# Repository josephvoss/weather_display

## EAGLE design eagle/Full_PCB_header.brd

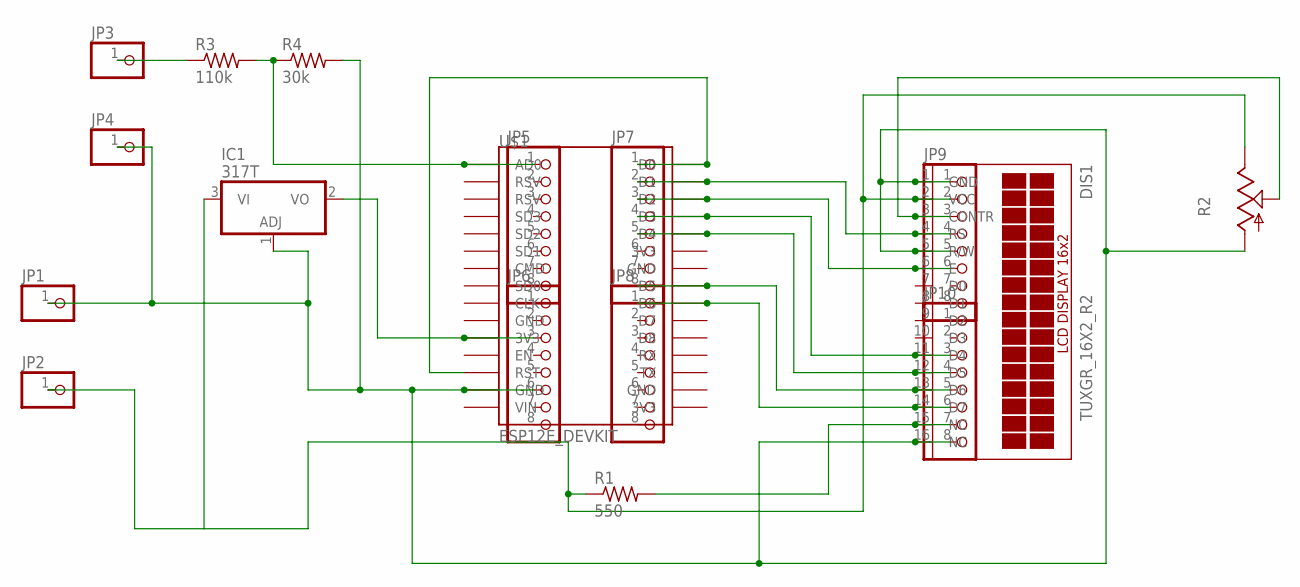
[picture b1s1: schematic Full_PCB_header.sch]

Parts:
DIS1: TUXGR_16X2_R2
IC1: 317T; TO220H
JP1, JP2, JP3, JP4: PINHD-1X1; 1X01
JP5, JP6, JP7, JP8, JP9, JP10: PINHD-1X8; 1X08
R1: 550; 0207/10
R2: TRIM_US-B25U; B25U
R3: 110k; 0207/10
R4: 30k; 0207/10
U$1: ESP12E_DEVKIT

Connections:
unnamed: JP5.1, R3.2, R4.1, U$1.AD0
unnamed: DIS1.2 (VCC), IC1.3 (VI), JP2.1, JP9.2, R1.1, R2.E
unnamed: DIS1.4 (RS), JP7.2, JP9.4, U$1.D1
unnamed: DIS1.15 (NC), JP10.7, R1.2
unnamed: DIS1.6 (E), JP7.3, JP9.6, U$1.D2
unnamed: DIS1.11 (D4), JP7.4, JP10.3, U$1.D3
unnamed: DIS1.12 (D5), JP7.5, JP10.4, U$1.D4
unnamed: DIS1.13 (D6), JP7.8, JP10.5, U$1.D5
unnamed: DIS1.14 (D7), JP8.1, JP10.6, U$1.D6
unnamed: IC1.2 (VO), JP6.3, U$1.3V3@0 (3V3)
unnamed: JP7.1, U$1.D0, U$1.RST
unnamed: DIS1.3 (CONTR), JP9.3, R2.S
unnamed: JP3.1, R3.1
unnamed: DIS1.1 (GND), DIS1.5 (R/W), DIS1.16 (NC), IC1.1 (ADJ), JP1.1, JP4.1, JP6.6, JP9.1, JP9.5, JP10.8, R2.A, R4.2, U$1.GND@1 (GND)

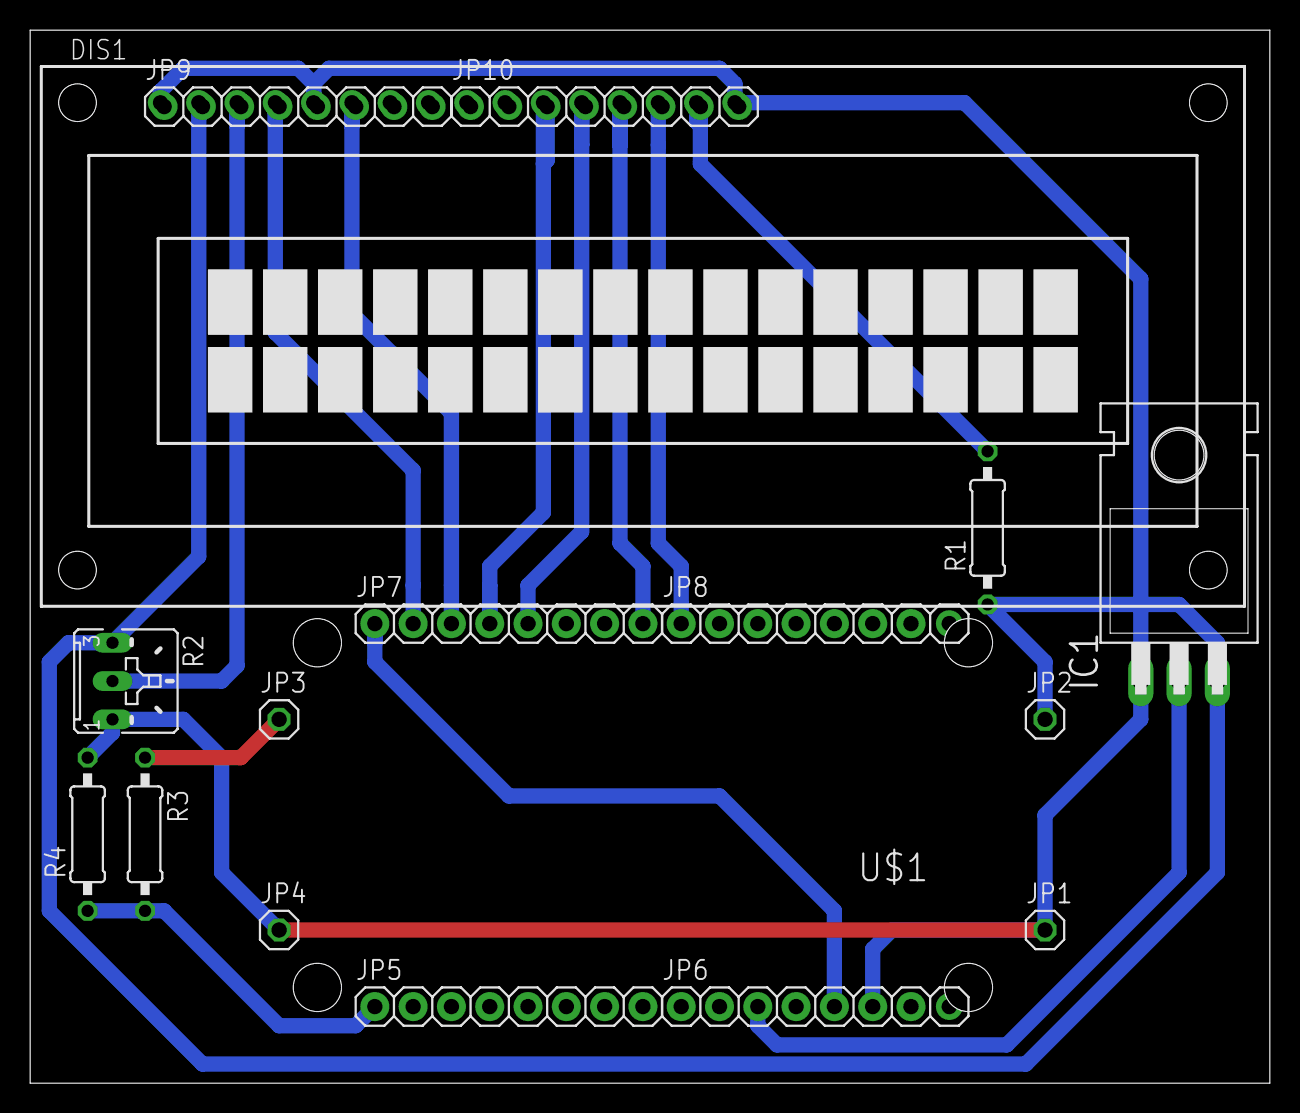
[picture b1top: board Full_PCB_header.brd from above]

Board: 2 copper layers, 82.2 x 69.8 mm, 17 parts (0 on the bottom side), 14 nets.

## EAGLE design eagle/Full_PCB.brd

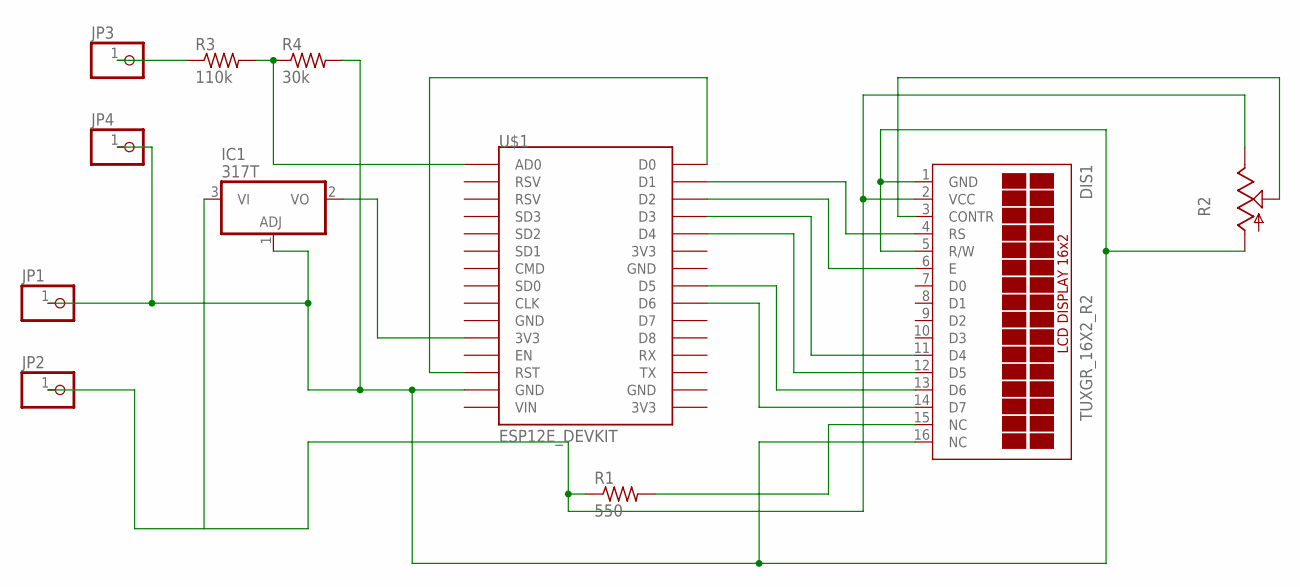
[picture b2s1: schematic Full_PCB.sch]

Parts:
DIS1: TUXGR_16X2_R2
IC1: 317T; TO220H
JP1, JP2, JP3, JP4: PINHD-1X1; 1X01
R1: 550; 0207/10
R2: TRIM_US-B25U; B25U
R3: 110k; 0207/10
R4: 30k; 0207/10
U$1: ESP12E_DEVKIT

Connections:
unnamed: R3.2, R4.1, U$1.AD0
unnamed: DIS1.2 (VCC), IC1.3 (VI), JP2.1, R1.1, R2.E
unnamed: DIS1.4 (RS), U$1.D1
unnamed: DIS1.15 (NC), R1.2
unnamed: DIS1.6 (E), U$1.D2
unnamed: DIS1.11 (D4), U$1.D3
unnamed: DIS1.12 (D5), U$1.D4
unnamed: DIS1.13 (D6), U$1.D5
unnamed: DIS1.14 (D7), U$1.D6
unnamed: IC1.2 (VO), U$1.3V3@0 (3V3)
unnamed: U$1.D0, U$1.RST
unnamed: DIS1.3 (CONTR), R2.S
unnamed: JP3.1, R3.1
unnamed: DIS1.1 (GND), DIS1.5 (R/W), DIS1.16 (NC), IC1.1 (ADJ), JP1.1, JP4.1, R2.A, R4.2, U$1.GND@1 (GND)

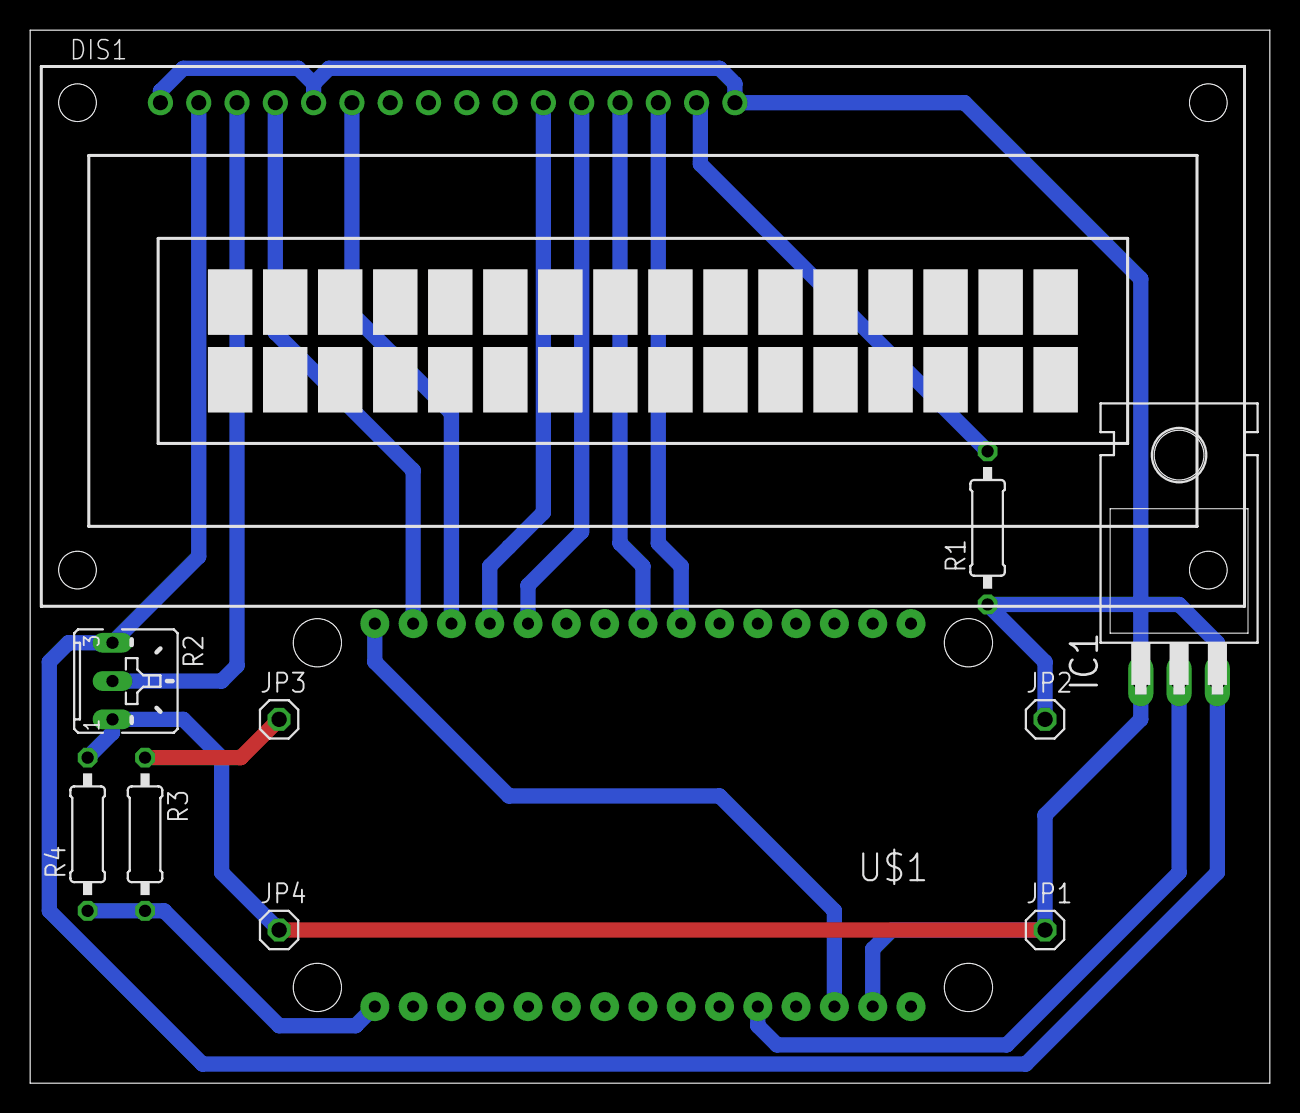
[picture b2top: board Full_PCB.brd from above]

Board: 2 copper layers, 82.2 x 69.8 mm, 11 parts (0 on the bottom side), 14 nets.

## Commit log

2017-03-18 Adds weather script as a daemon
2017-03-18 Changes communication profile to MQTT
    Orginally was reading a webpage that's continually updated via a
    cronjob. Now is updated by a message sent from the arduino client,
    which submits the voltage of the display. This voltage with the
    weather data is submitted to graphite on the server side. The server
    daemon also submits the weather data to sensor to display.
2017-03-18 Adding gitignore
2017-03-27 De-daemonizing script for use with systemd
2017-03-27 Adding service script to run as systemd
2017-03-27 Fixes typo
2017-03-29 Small bug fix to return current time
2017-04-03 Reworking callback function
2017-04-04 Fixes battery voltage conversion
2017-04-04 Fixes 24 hour rollover issue with grafana reporting
2017-05-16 Adding eagle files from pcb design
